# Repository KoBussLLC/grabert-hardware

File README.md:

# Grabert Keyboard Hardware

💻 🖥️ ⌨️ Open-source ~60% Mechanical Keyboard 🎉

Build Guide and additional information [here](doc/BUILDGUIDE.md)!

<details>
  <summary>Screen and Foot</summary>

</details>
<br/>
<details>
  <summary>PCB Images</summary>

</details>
<br/>

[PCB design video](https://youtu.be/ezk02GJ9iMs)

[Case design video](https://youtu.be/DsW-hKeB3mc)

## Features

- OLED Screen
- Rotary Knob
- Sandwich Mount Case
- POM Switch Plate
- [4 Layout Options](doc/BUILDGUIDE.md#preparation-and-layout-decision)
- 32-bit Microcontroller

### Powered by

- [QMK](https://github.com/qmk/qmk_firmware) ([KoBuss QMK Fork](https://github.com/KoBussLLC/qmk_firmware))
- [VIA](https://caniusevia.com/)

## PCB

This project uses KiCad 6 for electrical CAD

### Electrical Design Constraints
- No diode matrix enabled by LQFP 100 MCU Footprint
- 32-bit STM32 Microcontroller (STM32F072V8T6)
- USB-C
- PCB Mount Switches
- PCB Mount Stabilizers
- Push-Button Encoder
- 0.91" 128x32px I2C OLED Display (SSD1306)

### Changes
- V0 had incorrectly valued bypass capacitors. Testing showed no obvious issues, but it is not preferable.

## CAD

This project uses FreeCAD 0.19 for mechanical CAD

### Required Add-ons
- Assembly 4
- Fasteners
- kicadStepUpMod

### Mechanical Design Contraints
- ~60% Keyboard Layout
- 5 Layout Options
- Push Button Encoder
- OLED 128x32 Screen
- Fully Laser Cut Case
- POM Switch Plate
- 2mm diameter fasteners

### Acrylic Sheet Stackup

Main Case Stackup. "0" is the bottom of the case.

| Sheet Number | FreeCAD "Part" | Thickness | Material | Shape |
| - | - | - | - | - |
| 0 | bottom | 0.125 in | Acrylic |  |
| 1 | closed_spacer | 0.125 in | Acrylic |  |
| 2 | usb_spacer | 0.125 in | Acrylic |  *with feet |
| 3 | usb_spacer | 0.125 in | Acrylic |  *with feet |
| 4 | switch_plate | 0.0625 in | POM/Acetal |  |
| 5 | closed_spacer | 0.125 in | Acrylic |  |
| 6 | colored_top | 0.125 in | Acrylic |  |
| 7 | clear_top | 0.125 in | Acrylic |  |

#### Angled Foot Stackup

Foot stackup. "0" is closest to the case and is on the "top"

| Sheet Number | FreeCAD "Part" | Thickness | Material |
| - | - | - | - |
| 0 | foot_0 | 0.125 in | Acrylic |
| 1 | foot_1 | 0.125 in | Acrylic |
| 2 | foot_2 | 0.125 in | Acrylic |

## License
MIT License

Copyright (c) 2021 KoBuss LLC

Permission is hereby granted, free of charge, to any person obtaining a copy of this hardware, software, and associated documentation files (the "Product"), to deal in the Product without restriction, including without limitation the rights to use, copy, modify, merge, publish, distribute, sublicense, and/or sell copies of the Product, and to permit persons to whom the Product is furnished to do so, subject to the following conditions:

The above copyright notice and this permission notice shall be included in all copies or substantial portions of the Product.

THE PRODUCT IS PROVIDED "AS IS", WITHOUT WARRANTY OF ANY KIND, EXPRESS OR IMPLIED, INCLUDING BUT NOT LIMITED TO THE WARRANTIES OF MERCHANTABILITY, FITNESS FOR A PARTICULAR PURPOSE AND NONINFRINGEMENT. IN NO EVENT SHALL THE AUTHORS OR COPYRIGHT HOLDERS BE LIABLE FOR ANY CLAIM, DAMAGES OR OTHER LIABILITY, WHETHER IN AN ACTION OF CONTRACT, TORT OR OTHERWISE, ARISING FROM, OUT OF OR IN CONNECTION WITH THE PRODUCT OR THE USE OR OTHER DEALINGS IN THE PRODUCT.

### For the Keyboard Community
You can produce and sell this keyboard. KoBuss LLC is not liable. Creator attribution is preferred but not required.

### License Change?
We initially licensed this under the Creative Commons Attribution-NonCommercial 4.0 International License, but have since decided to change it to MIT.
This would not be appropriate if the product was in production and had been forked/derived, but because we made the license change early on we deemed it acceptable.
If you have any issues with this change, please contact us directly.

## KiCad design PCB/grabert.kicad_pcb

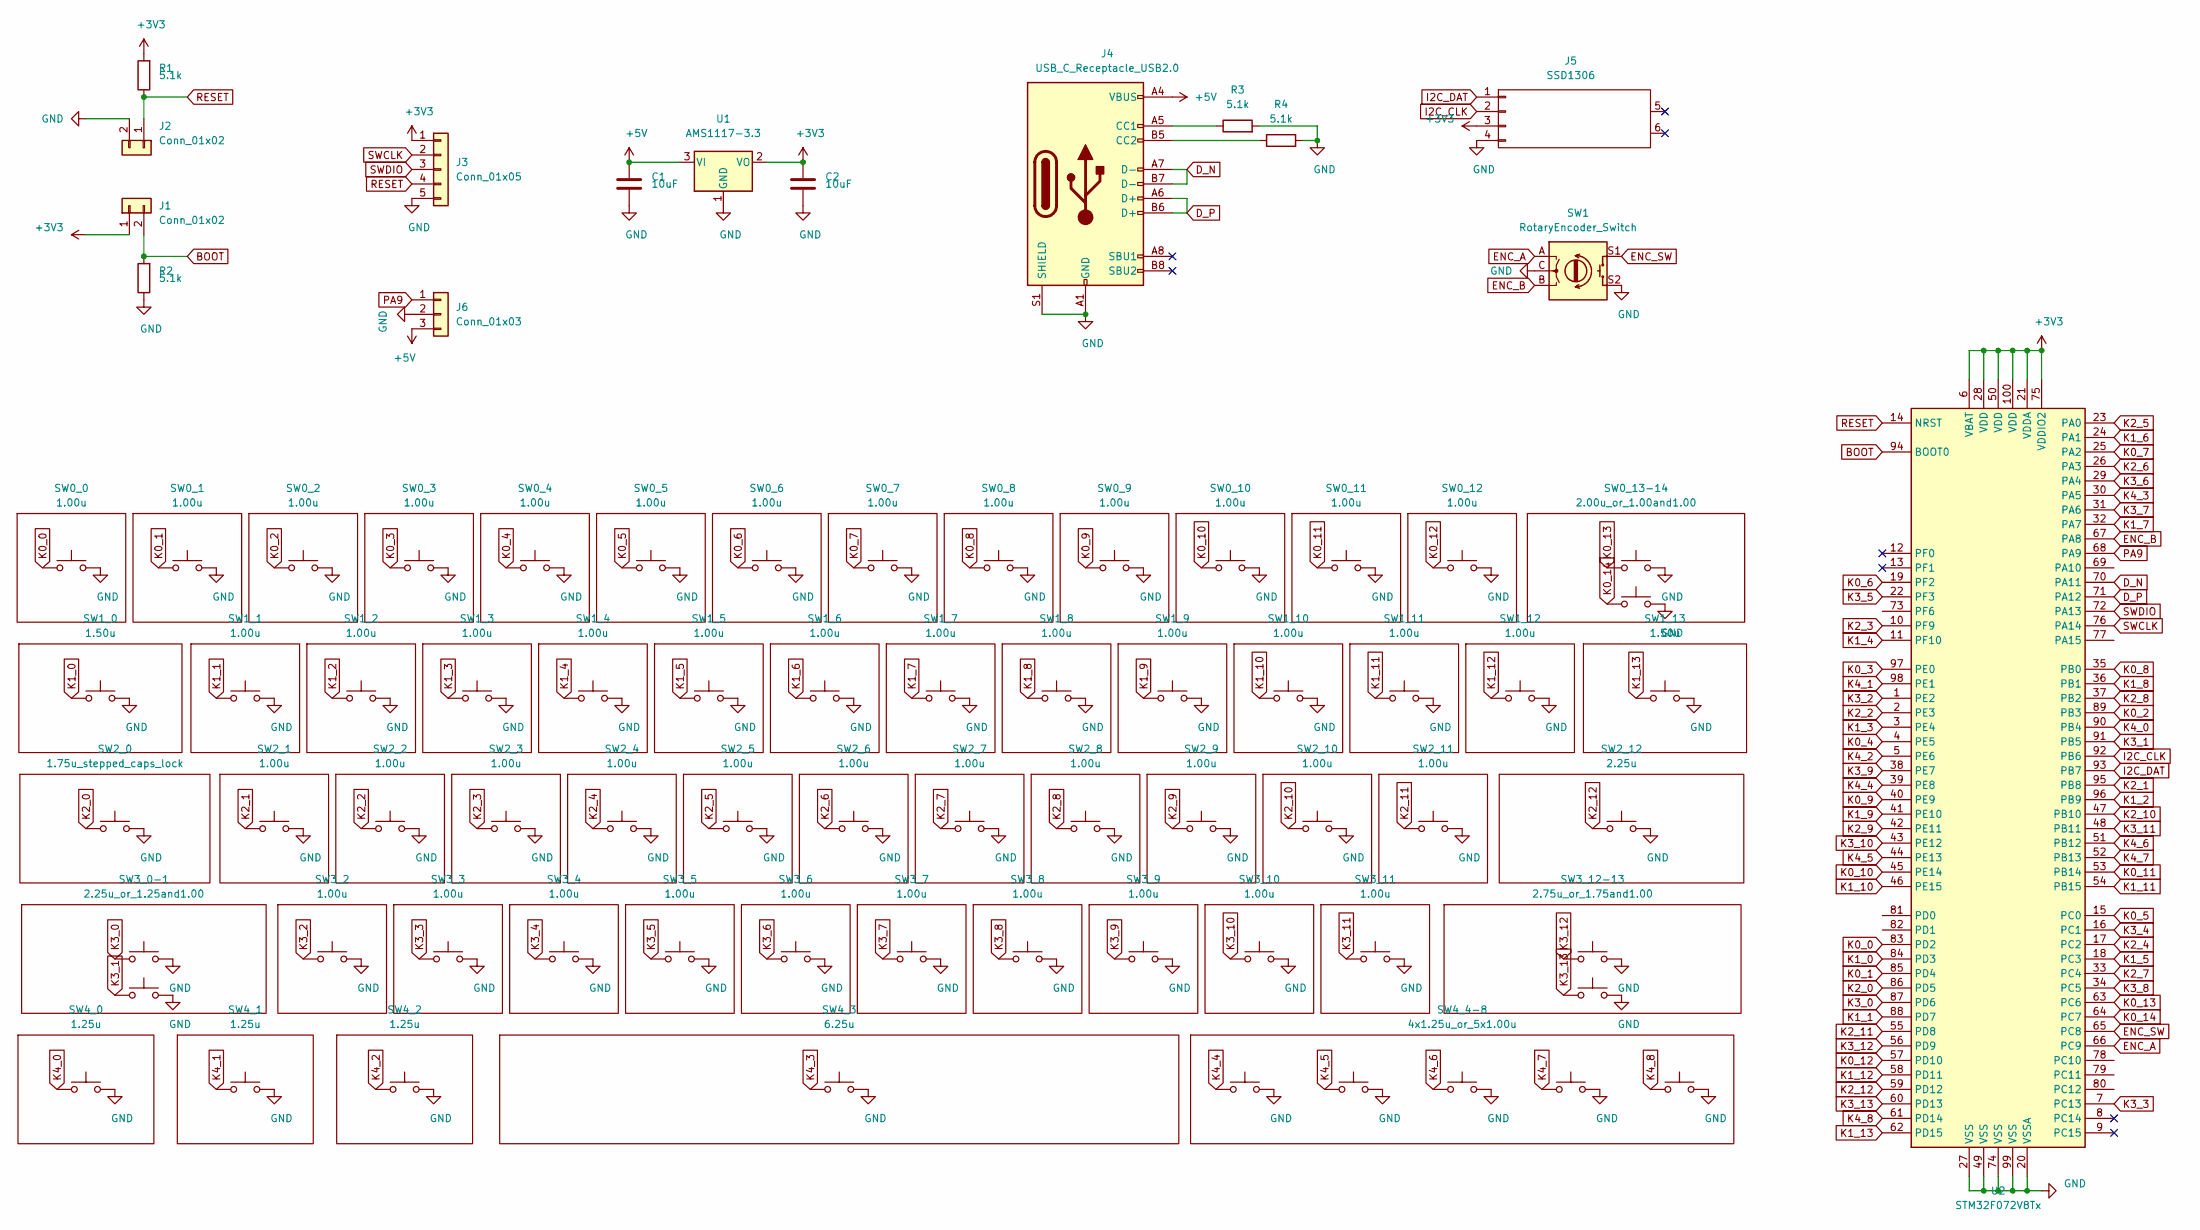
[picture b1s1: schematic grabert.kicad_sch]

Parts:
C1, C2: 10uF; C_0603_1608Metric
J1, J2: Conn_01x02; PinHeader_1x02_P2.54mm_Vertical
J3: Conn_01x05; PinHeader_1x05_P2.54mm_Vertical
J4: USB_C_Receptacle_USB2.0; U262-161N-4BVC11
J5: SSD1306
J6: Conn_01x03; PinHeader_1x03_P2.54mm_Vertical
R1, R2, R3, R4: 5.1k; R_0603_1608Metric
SW0_0, SW0_1, SW0_2, SW0_3, SW0_4, SW0_5, SW0_6, SW0_7, SW0_8, SW0_9, SW0_10, SW0_11, SW0_12, SW1_1, SW1_2, SW1_3, SW1_4, SW1_5, SW1_6, SW1_7, SW1_8, SW1_9, SW1_10, SW1_11, SW1_12, SW2_1, SW2_2, SW2_3, SW2_4, SW2_5, SW2_6, SW2_7, SW2_8, SW2_9, SW2_10, SW2_11, SW3_2, SW3_3, SW3_4, SW3_5, SW3_6, SW3_7, SW3_8, SW3_9, SW3_10, SW3_11: 1.00u; MX_1u
SW0_13-14: 2.00u_or_1.00and1.00; MX_2.00u_or_1.00and1.00
SW1: RotaryEncoder_Switch; PEC11R-4220K-S0024
SW1_0, SW1_13: 1.50u; MX_1.50u
SW2_0: 1.75u_stepped_caps_lock; MX_1.75u_stepped_caps
SW2_12: 2.25u; MX_2.25u
SW3_0-1: 2.25u_or_1.25and1.00; MX_2.25u_or_1.25and1.00
SW3_12-13: 2.75u_or_1.75and1.00; MX_2.75u_or_1.75and1.00
SW4_0, SW4_1, SW4_2: 1.25u; MX_1.25
SW4_3: 6.25u; MX_6.25u
SW4_4-8: 4x1.25u_or_5x1.00u; MX_4x1.25u_or_5x1.00u
U1: AMS1117-3.3; SOT-223-3_TabPin2
U2: STM32F072V8Tx; LQFP-100_14x14mm_P0.5mm

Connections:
+3V3: C2.1, J1.1, J3.1, J5.3 (VCC), R1.2, U1.2 (VO), U2.6 (VBAT), U2.21 (VDDA), U2.28 (VDD), U2.50 (VDD), U2.75 (VDDIO2), U2.100 (VDD)
+5V: C1.1, J4.A4 (VBUS), J4.A9 (VBUS), J4.B4 (VBUS), J4.B9 (VBUS), J6.3, U1.3 (VI)
BOOT: J1.2, R2.2, U2.94 (BOOT0)
D_N: J4.A7 (D-), J4.B7 (D-), U2.70 (PA11)
D_P: J4.A6 (D+), J4.B6 (D+), U2.71 (PA12)
ENC_A: SW1.A, U2.66 (PC9)
ENC_B: SW1.B, U2.67 (PA8)
ENC_SW: SW1.S1, U2.65 (PC8)
GND: C1.2, C2.2, J2.2, J3.5, J4.A1 (GND), J4.A12 (GND), J4.B1 (GND), J4.B12 (GND), J4.S1 (SHIELD), J5.4 (GND), J6.2, R2.1, R3.2, R4.2, SW0_0.2, SW0_1.2, SW0_2.2, SW0_3.2, SW0_4.2, SW0_5.2, SW0_6.2, SW0_7.2, SW0_8.2, SW0_9.2, SW0_10.2, SW0_11.2, SW0_12.2, SW0_13-14.2, SW0_13-14.4, SW1.C, SW1.S2, SW1_0.2, SW1_1.2, SW1_2.2, SW1_3.2, SW1_4.2, SW1_5.2, SW1_6.2, SW1_7.2, SW1_8.2, SW1_9.2, SW1_10.2, SW1_11.2, SW1_12.2, SW1_13.2, SW2_0.2, SW2_1.2, SW2_2.2, SW2_3.2, SW2_4.2, SW2_5.2, SW2_6.2, SW2_7.2, SW2_8.2, SW2_9.2, SW2_10.2, SW2_11.2, SW2_12.2, SW3_0-1.2, SW3_0-1.4, SW3_2.2, SW3_3.2, SW3_4.2, SW3_5.2, SW3_6.2, SW3_7.2, SW3_8.2, SW3_9.2, SW3_10.2, SW3_11.2, SW3_12-13.2, SW3_12-13.4, SW4_0.2, SW4_1.2, SW4_2.2, SW4_3.2, SW4_4-8.2, SW4_4-8.4, SW4_4-8.6, SW4_4-8.8, SW4_4-8.10, U1.1 (GND), U2.20 (VSSA), U2.27 (VSS), U2.49 (VSS), U2.74 (VSS), U2.99 (VSS)
I2C_CLK: J5.2 (SCL), U2.92 (PB6)
I2C_DAT: J5.1 (SDA), U2.93 (PB7)
K0_0: SW0_0.1, U2.83 (PD2)
K0_1: SW0_1.1, U2.85 (PD4)
K0_2: SW0_2.1, U2.89 (PB3)
K0_3: SW0_3.1, U2.97 (PE0)
K0_4: SW0_4.1, U2.4 (PE5)
K0_5: SW0_5.1, U2.15 (PC0)
K0_6: SW0_6.1, U2.19 (PF2)
K0_7: SW0_7.1, U2.25 (PA2)
K0_8: SW0_8.1, U2.35 (PB0)
K0_9: SW0_9.1, U2.40 (PE9)
K0_10: SW0_10.1, U2.45 (PE14)
K0_11: SW0_11.1, U2.53 (PB14)
K0_12: SW0_12.1, U2.57 (PD10)
K0_13: SW0_13-14.1, U2.63 (PC6)
K0_14: SW0_13-14.3, U2.64 (PC7)
K1_0: SW1_0.1, U2.84 (PD3)
K1_1: SW1_1.1, U2.88 (PD7)
K1_2: SW1_2.1, U2.96 (PB9)
K1_3: SW1_3.1, U2.3 (PE4)
K1_4: SW1_4.1, U2.11 (PF10)
K1_5: SW1_5.1, U2.18 (PC3)
K1_6: SW1_6.1, U2.24 (PA1)
K1_7: SW1_7.1, U2.32 (PA7)
K1_8: SW1_8.1, U2.36 (PB1)
K1_9: SW1_9.1, U2.41 (PE10)
K1_10: SW1_10.1, U2.46 (PE15)
K1_11: SW1_11.1, U2.54 (PB15)
K1_12: SW1_12.1, U2.58 (PD11)
K1_13: SW1_13.1, U2.62 (PD15)
K2_0: SW2_0.1, U2.86 (PD5)
K2_1: SW2_1.1, U2.95 (PB8)
K2_2: SW2_2.1, U2.2 (PE3)
K2_3: SW2_3.1, U2.10 (PF9)
K2_4: SW2_4.1, U2.17 (PC2)
K2_5: SW2_5.1, U2.23 (PA0)
K2_6: SW2_6.1, U2.26 (PA3)
K2_7: SW2_7.1, U2.33 (PC4)
K2_8: SW2_8.1, U2.37 (PB2)
K2_9: SW2_9.1, U2.42 (PE11)
K2_10: SW2_10.1, U2.47 (PB10)
K2_11: SW2_11.1, U2.55 (PD8)
K2_12: SW2_12.1, U2.59 (PD12)
K3_0: SW3_0-1.1, U2.87 (PD6)
K3_1: SW3_0-1.3, U2.91 (PB5)
K3_2: SW3_2.1, U2.1 (PE2)
K3_3: SW3_3.1, U2.7 (PC13)
K3_4: SW3_4.1, U2.16 (PC1)
K3_5: SW3_5.1, U2.22 (PF3)
K3_6: SW3_6.1, U2.29 (PA4)
K3_7: SW3_7.1, U2.31 (PA6)
K3_8: SW3_8.1, U2.34 (PC5)
K3_9: SW3_9.1, U2.38 (PE7)
K3_10: SW3_10.1, U2.43 (PE12)
K3_11: SW3_11.1, U2.48 (PB11)
K3_12: SW3_12-13.1, U2.56 (PD9)
K3_13: SW3_12-13.3, U2.60 (PD13)
K4_0: SW4_0.1, U2.90 (PB4)
K4_1: SW4_1.1, U2.98 (PE1)
K4_2: SW4_2.1, U2.5 (PE6)
K4_3: SW4_3.1, U2.30 (PA5)
K4_4: SW4_4-8.1, U2.39 (PE8)
K4_5: SW4_4-8.3, U2.44 (PE13)
K4_6: SW4_4-8.5, U2.51 (PB12)
K4_7: SW4_4-8.7, U2.52 (PB13)
K4_8: SW4_4-8.9, U2.61 (PD14)
unnamed: J4.A5 (CC1), R3.1
unnamed: J4.B5 (CC2), R4.1
PA9: J6.1, U2.68 (PA9)
RESET: J2.1, J3.4, R1.1, U2.14 (NRST)
SWCLK: J3.2, U2.76 (PA14)
SWDIO: J3.3, U2.72 (PA13)

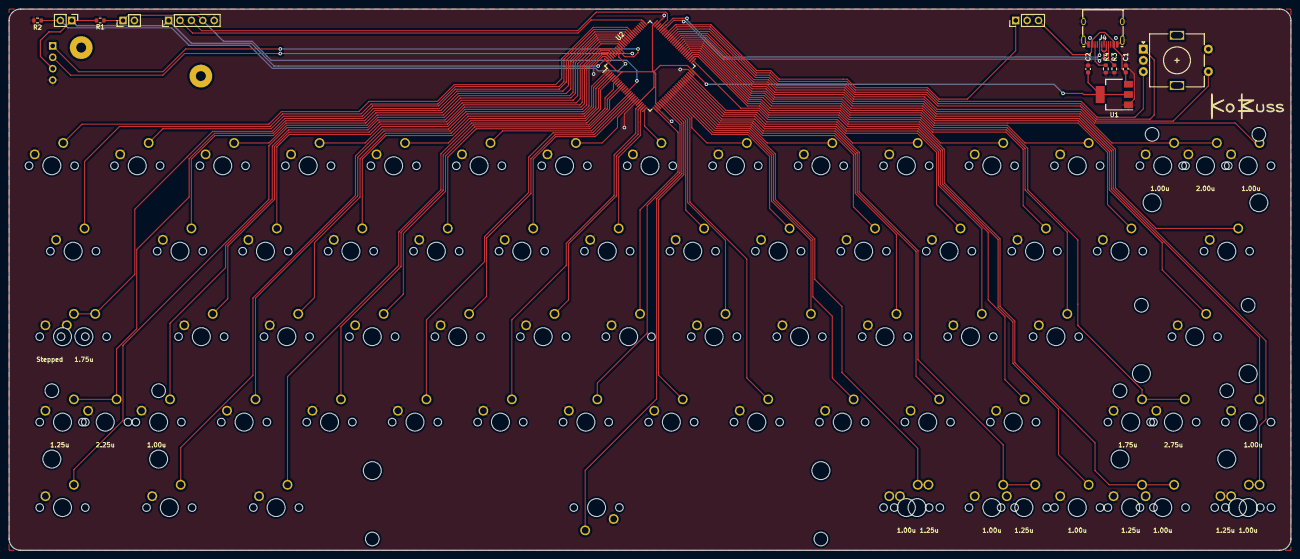
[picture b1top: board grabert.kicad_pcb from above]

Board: 2 copper layers, 285.8 x 120.7 mm, 75 parts (1 on the bottom side), 82 nets.

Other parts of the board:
Ref**: Val**; kobuss_name
Ref**#2: Val**; kobuss_name

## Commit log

2020-11-18 pcb with peripherals but no switches
2020-11-18 switches added
2020-11-18 switches placed
2020-11-18 fixed component positions
2020-11-18 corrected OLED pads
2020-11-18 Switch inputs linked to mcu
2020-11-18 right switch traces
2020-11-19 Routed PCB
2020-11-19 V0 prelim
2020-11-29 solder mask bridge minimum
2020-11-29 V0 KiCad 5.99 PCB (#1)
    * pcb with peripherals but no switches
    * switches added
    * switches placed
    * fixed component positions
    * corrected OLED pads
    * Switch inputs linked to mcu
2020-11-30 Initial switchplate CAD
2020-12-01 Switch plate features complete
2020-12-05 Acrylic Case Assembled
2020-12-05 pcb added to cad with feet
2020-12-06 LICENSE
2020-12-06 case adjustments
2020-12-16 Initial proto laser cut
2021-01-04 Initial documentation and build guide
2021-01-04 markdown table space
2021-01-04 markdown pic space
2021-01-05 build guide tweaks
2021-01-06 additional firmware flashing documentation
2021-01-09 full keyboard images added
2021-01-25 doc improvements
2021-01-31 typos
2021-03-01 design video links
2021-04-03 MIT LICENSE
2021-04-06 pcb: added 100nF bypass caps
